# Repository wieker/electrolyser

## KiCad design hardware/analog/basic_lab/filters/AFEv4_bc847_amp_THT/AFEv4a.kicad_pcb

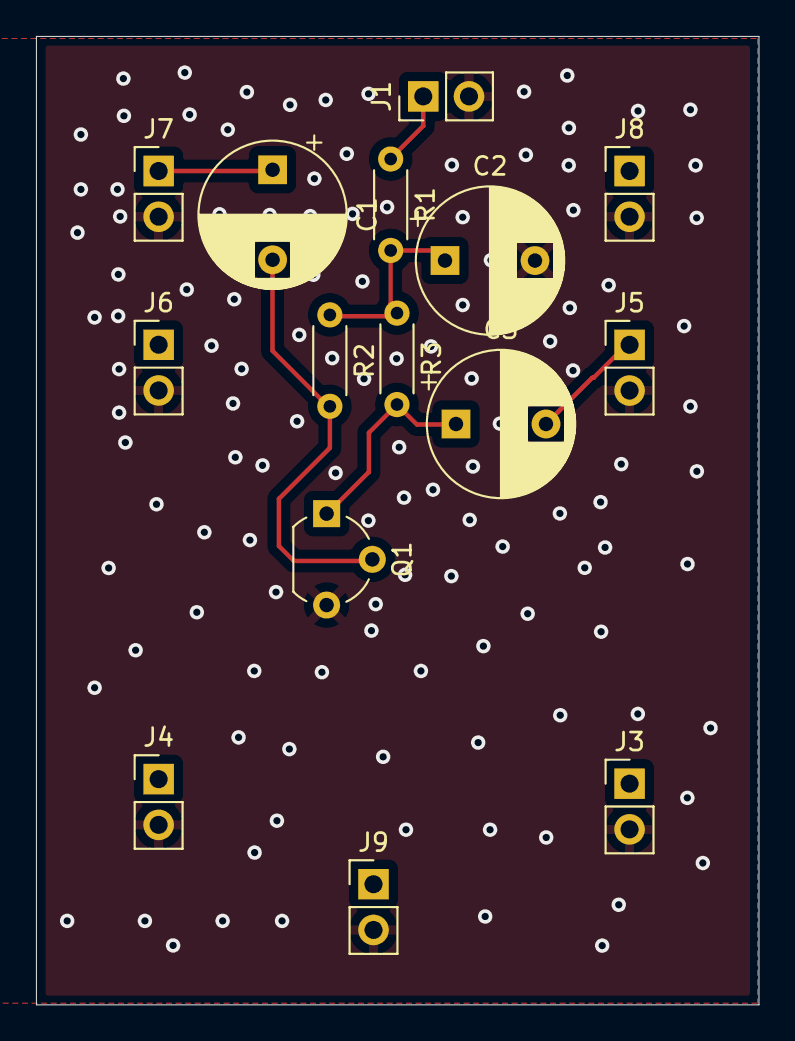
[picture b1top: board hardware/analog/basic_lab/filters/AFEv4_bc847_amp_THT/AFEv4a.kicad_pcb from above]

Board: 2 copper layers, 40.1 x 53.8 mm, 15 parts (0 on the bottom side), 7 nets.

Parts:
C1, C2, C3: C; CP_Radial_D8.0mm_P5.00mm
J1: Conn_01x02_Male; PinHeader_1x02_P2.54mm_Vertical
J3, J4, J5, J6, J7, J8, J9: Connector_Generic_Conn_01x02; PinHeader_1x02_P2.54mm_Vertical
Q1: BC547; TO-92_Wide
R1: R; R_Axial_DIN0204_L3.6mm_D1.6mm_P5.08mm_Horizontal
R2: 100 kOhm; R_Axial_DIN0204_L3.6mm_D1.6mm_P5.08mm_Horizontal
R3: 100 Ohm; R_Axial_DIN0204_L3.6mm_D1.6mm_P5.08mm_Horizontal

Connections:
GND: C2.2, J1.2, J3.2, J4.2, J5.2, J6.2, J7.2, J8.2, J9.2, Q1.3 (E)
unnamed: C1.2, Q1.2 (B), R2.2
unnamed: C2.1, R1.2, R2.1, R3.1
unnamed: C3.1, Q1.1 (C), R3.2
unnamed: J1.1, R1.1
bpf_ant: C3.2, J5.1
bpf_lvds: C1.1, J7.1

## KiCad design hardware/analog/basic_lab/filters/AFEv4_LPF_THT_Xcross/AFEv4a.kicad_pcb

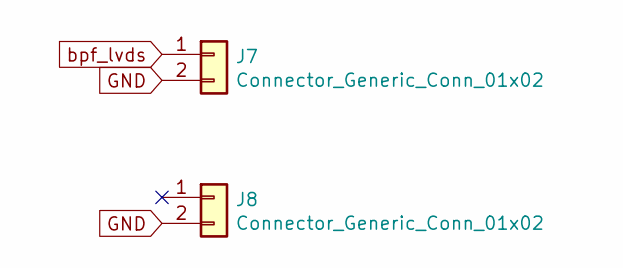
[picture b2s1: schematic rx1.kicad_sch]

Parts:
J7, J8: Connector_Generic_Conn_01x02; PinHeader_1x02_P2.54mm_Vertical

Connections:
GND: J7.2, J8.2; also elsewhere on the board
bpf_lvds: J7.1; also elsewhere on the board

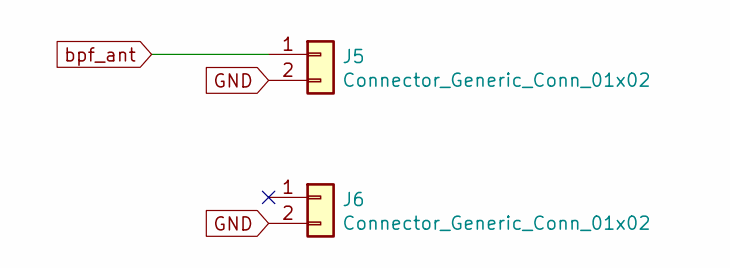
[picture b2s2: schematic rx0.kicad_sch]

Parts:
J5, J6: Connector_Generic_Conn_01x02; PinHeader_1x02_P2.54mm_Vertical

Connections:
GND: J5.2, J6.2; also elsewhere on the board
bpf_ant: J5.1; also elsewhere on the board

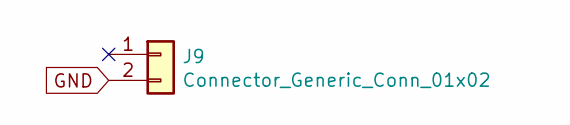
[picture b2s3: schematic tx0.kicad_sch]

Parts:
J9: Connector_Generic_Conn_01x02; PinHeader_1x02_P2.54mm_Vertical

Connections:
GND: J9.2; also elsewhere on the board

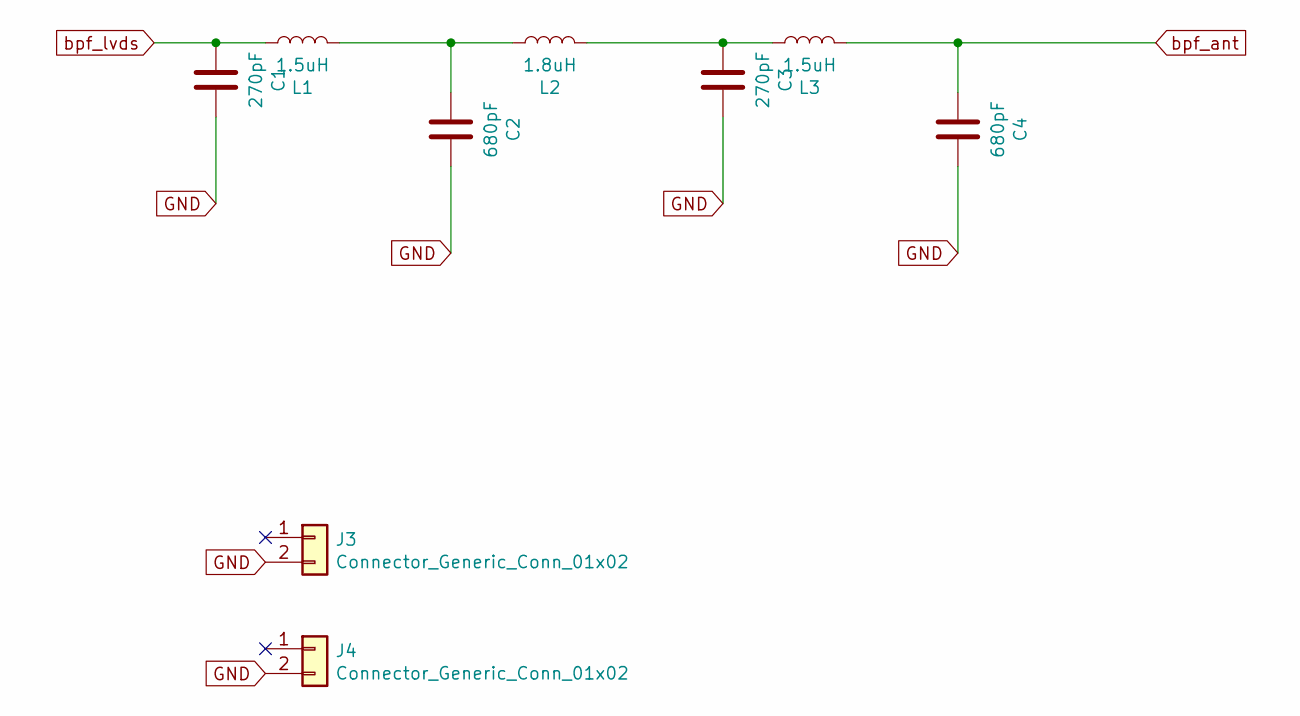
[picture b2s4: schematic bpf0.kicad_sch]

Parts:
C1, C3: 270pF; CP_Radial_D8.0mm_P5.00mm
C2, C4: 680pF; CP_Radial_D8.0mm_P5.00mm
J3, J4: Connector_Generic_Conn_01x02; PinHeader_1x02_P2.54mm_Vertical
L1, L3: 1.5uH; L_Axial_L9.5mm_D4.0mm_P12.70mm_Horizontal_Fastron_SMCC
L2: 1.8uH; L_Axial_L9.5mm_D4.0mm_P12.70mm_Horizontal_Fastron_SMCC

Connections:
GND: C1.1, C2.1, C3.1, C4.1, J3.2, J4.2; also elsewhere on the board
unnamed: C2.2, L1.2, L2.1
unnamed: C3.2, L2.2, L3.1
bpf_ant: C4.2, L3.2; also elsewhere on the board
bpf_lvds: C1.2, L1.1; also elsewhere on the board

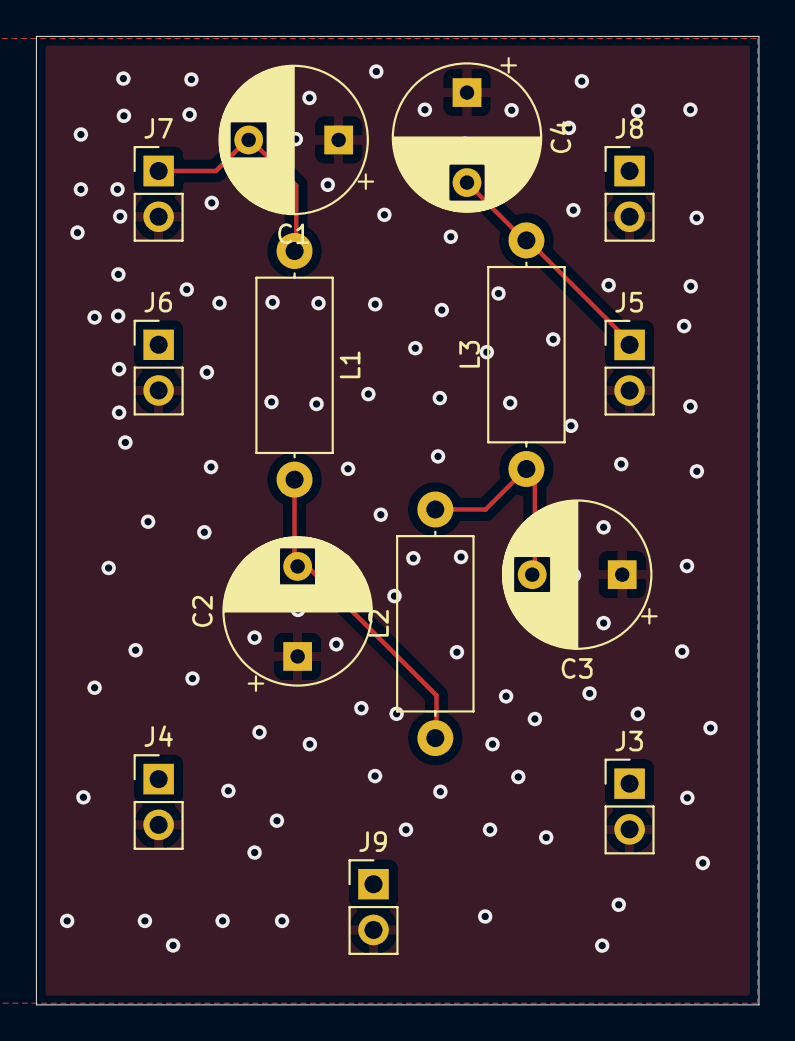
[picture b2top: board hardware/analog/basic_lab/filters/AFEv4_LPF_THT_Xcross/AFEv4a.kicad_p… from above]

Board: 2 copper layers, 40.1 x 53.8 mm, 14 parts (0 on the bottom side), 5 nets.

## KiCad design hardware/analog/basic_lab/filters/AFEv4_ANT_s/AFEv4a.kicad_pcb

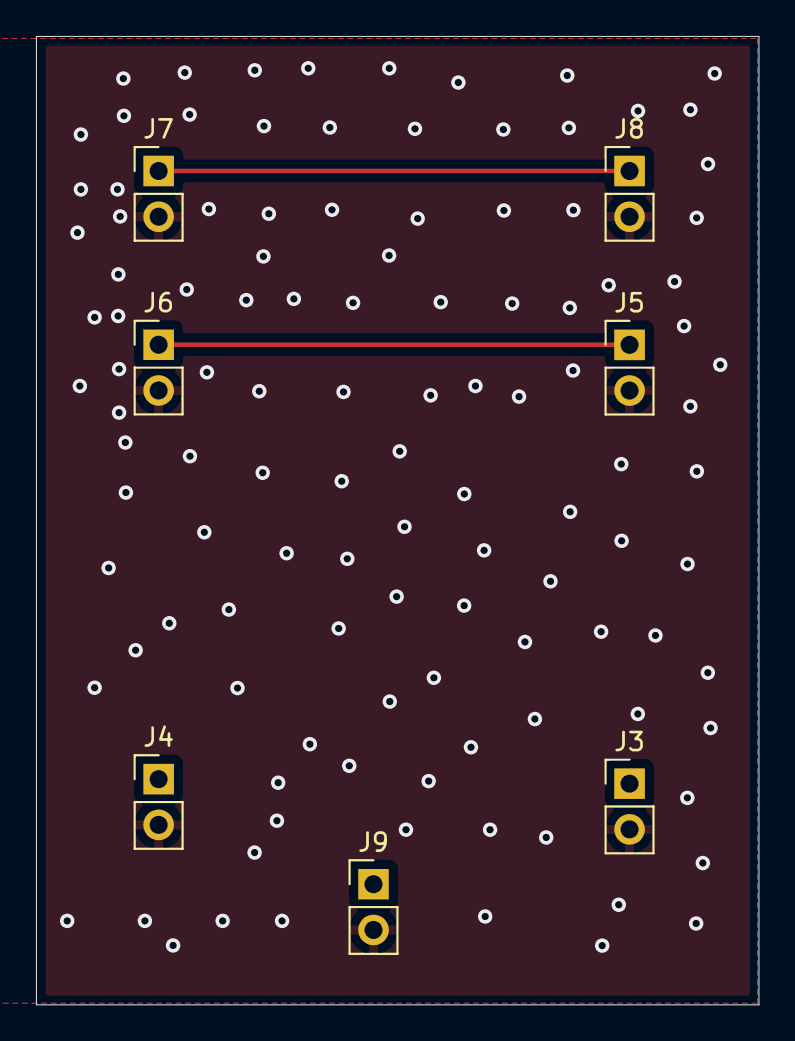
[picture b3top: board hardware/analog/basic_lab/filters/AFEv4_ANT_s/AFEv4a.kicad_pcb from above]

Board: 2 copper layers, 40.1 x 53.8 mm, 7 parts (0 on the bottom side), 3 nets.

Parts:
J3, J4, J5, J6, J7, J8, J9: Connector_Generic_Conn_01x02; PinHeader_1x02_P2.54mm_Vertical

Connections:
GND: J3.2, J4.2, J5.2, J6.2, J7.2, J8.2, J9.2
unnamed: J5.1, J6.1
bpf_lvds: J7.1, J8.1

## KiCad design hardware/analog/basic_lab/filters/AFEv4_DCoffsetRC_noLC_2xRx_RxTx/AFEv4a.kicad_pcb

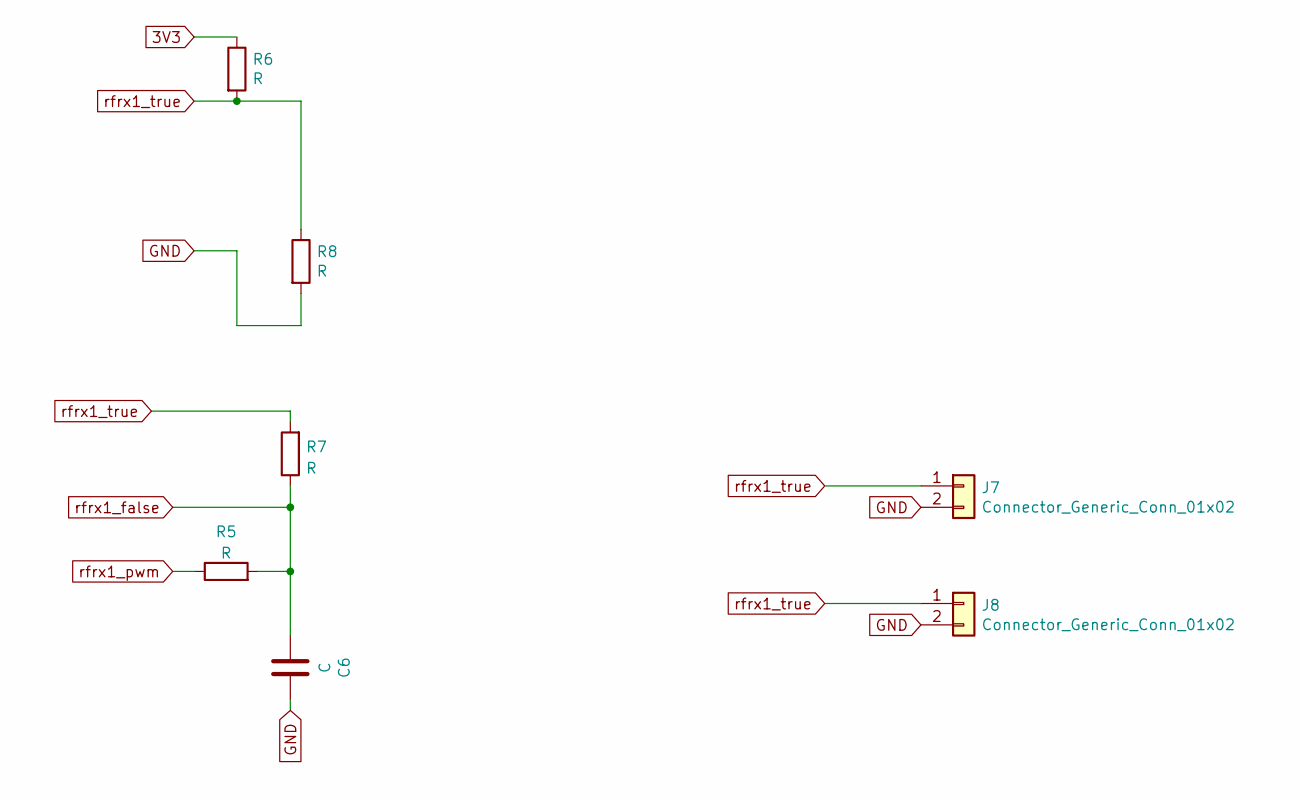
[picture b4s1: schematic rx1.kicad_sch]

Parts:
C6: C; C_Axial_L3.8mm_D2.6mm_P7.50mm_Horizontal
J7, J8: Connector_Generic_Conn_01x02; PinHeader_1x02_P2.54mm_Vertical
R5, R6, R7, R8: R; R_Axial_DIN0207_L6.3mm_D2.5mm_P5.08mm_Vertical

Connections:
3V3: R6.1; also elsewhere on the board
GND: C6.1, J7.2, J8.2, R8.2; also elsewhere on the board
rfrx1_false: C6.2, R5.2, R7.1; also elsewhere on the board
rfrx1_pwm: R5.1; also elsewhere on the board
rfrx1_true: J7.1, J8.1, R6.2, R7.2, R8.1; also elsewhere on the board

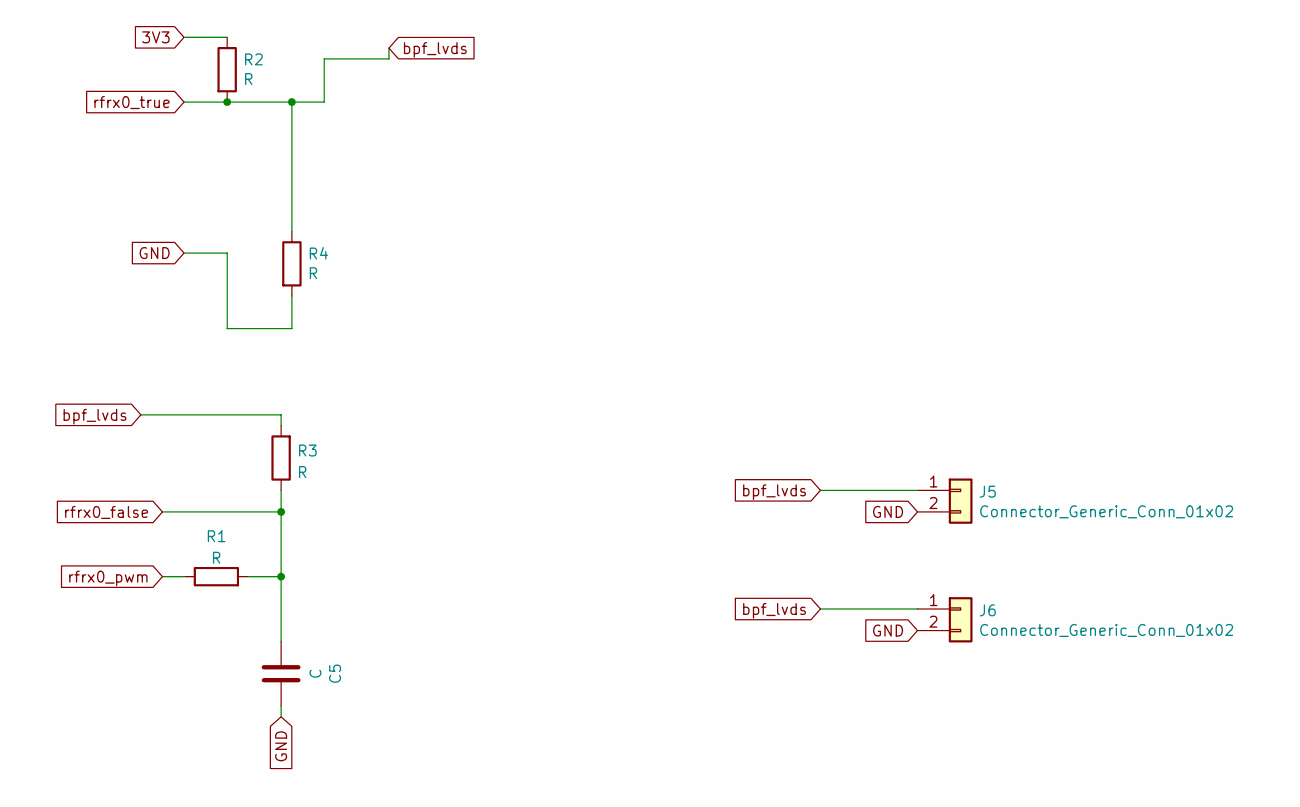
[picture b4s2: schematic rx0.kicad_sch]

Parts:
C5: C; C_1206_3216Metric
J5, J6: Connector_Generic_Conn_01x02; PinHeader_1x02_P2.54mm_Vertical
R1, R2, R3, R4: R; R_1206_3216Metric

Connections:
3V3: R2.1; also elsewhere on the board
GND: C5.1, J5.2, J6.2, R4.2; also elsewhere on the board
bpf_lvds: J5.1, J6.1, R2.2, R3.2, R4.1; also elsewhere on the board
rfrx0_false: C5.2, R1.2, R3.1; also elsewhere on the board
rfrx0_pwm: R1.1; also elsewhere on the board

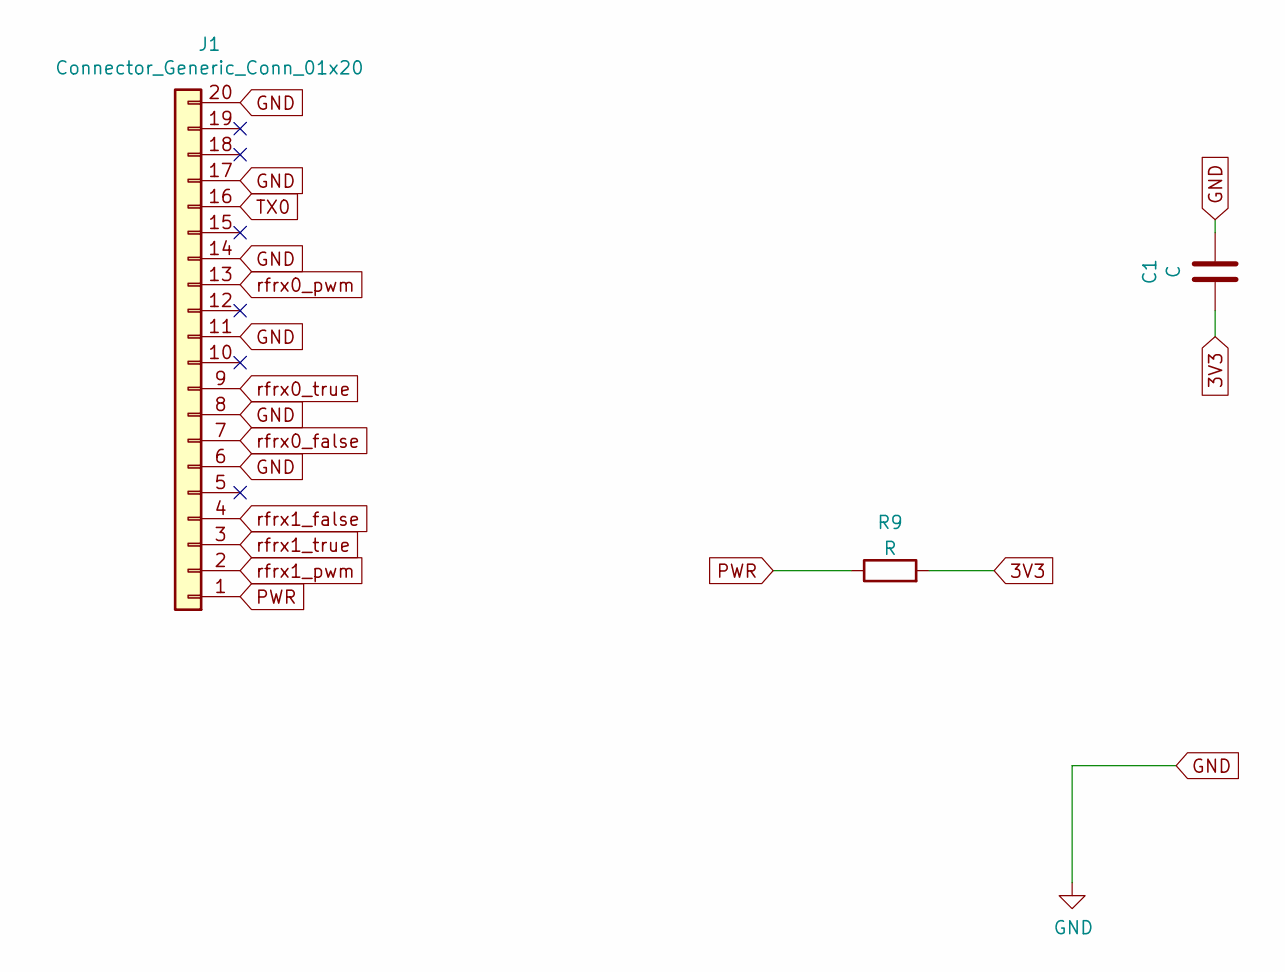
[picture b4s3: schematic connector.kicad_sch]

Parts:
C1: C; C_1206_3216Metric
J1: Connector_Generic_Conn_01x20; PinHeader_1x20_P2.54mm_Vertical
R9: R; R_0805_2012Metric

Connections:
3V3: C1.2, R9.2; also elsewhere on the board
GND: C1.1, J1.6, J1.8, J1.11, J1.14, J1.17, J1.20; also elsewhere on the board
PWR: J1.1, R9.1
TX0: J1.16; also elsewhere on the board
bpf_lvds: J1.9; also elsewhere on the board
rfrx0_false: J1.7; also elsewhere on the board
rfrx0_pwm: J1.13; also elsewhere on the board
rfrx1_false: J1.4; also elsewhere on the board
rfrx1_pwm: J1.2; also elsewhere on the board
rfrx1_true: J1.3; also elsewhere on the board

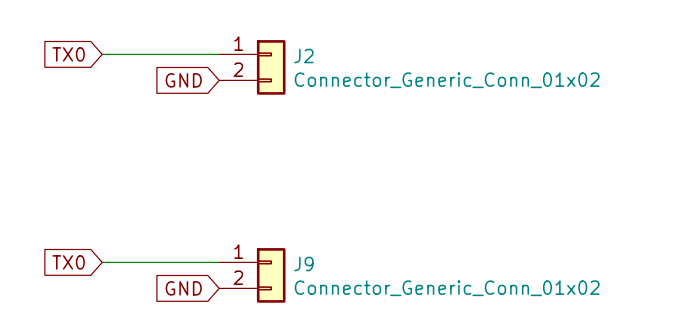
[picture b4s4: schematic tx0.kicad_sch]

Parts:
J2, J9: Connector_Generic_Conn_01x02; PinHeader_1x02_P2.54mm_Vertical

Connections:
GND: J2.2, J9.2; also elsewhere on the board
TX0: J2.1, J9.1; also elsewhere on the board

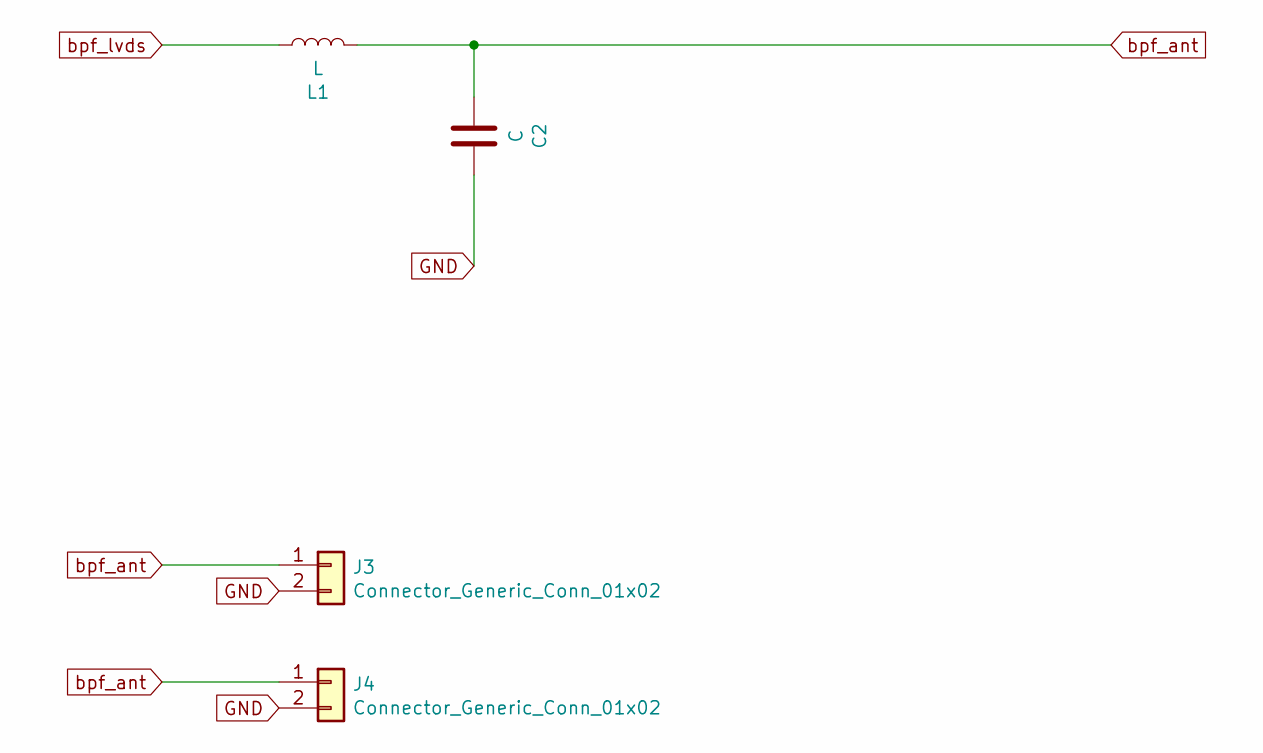
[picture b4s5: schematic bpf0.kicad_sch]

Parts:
C2: C; C_1206_3216Metric
J3, J4: Connector_Generic_Conn_01x02; PinHeader_1x02_P2.54mm_Vertical
L1: L; L_1206_3216Metric

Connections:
GND: C2.1, J3.2, J4.2; also elsewhere on the board
bpf_ant: C2.2, J3.1, J4.1, L1.2
bpf_lvds: L1.1; also elsewhere on the board

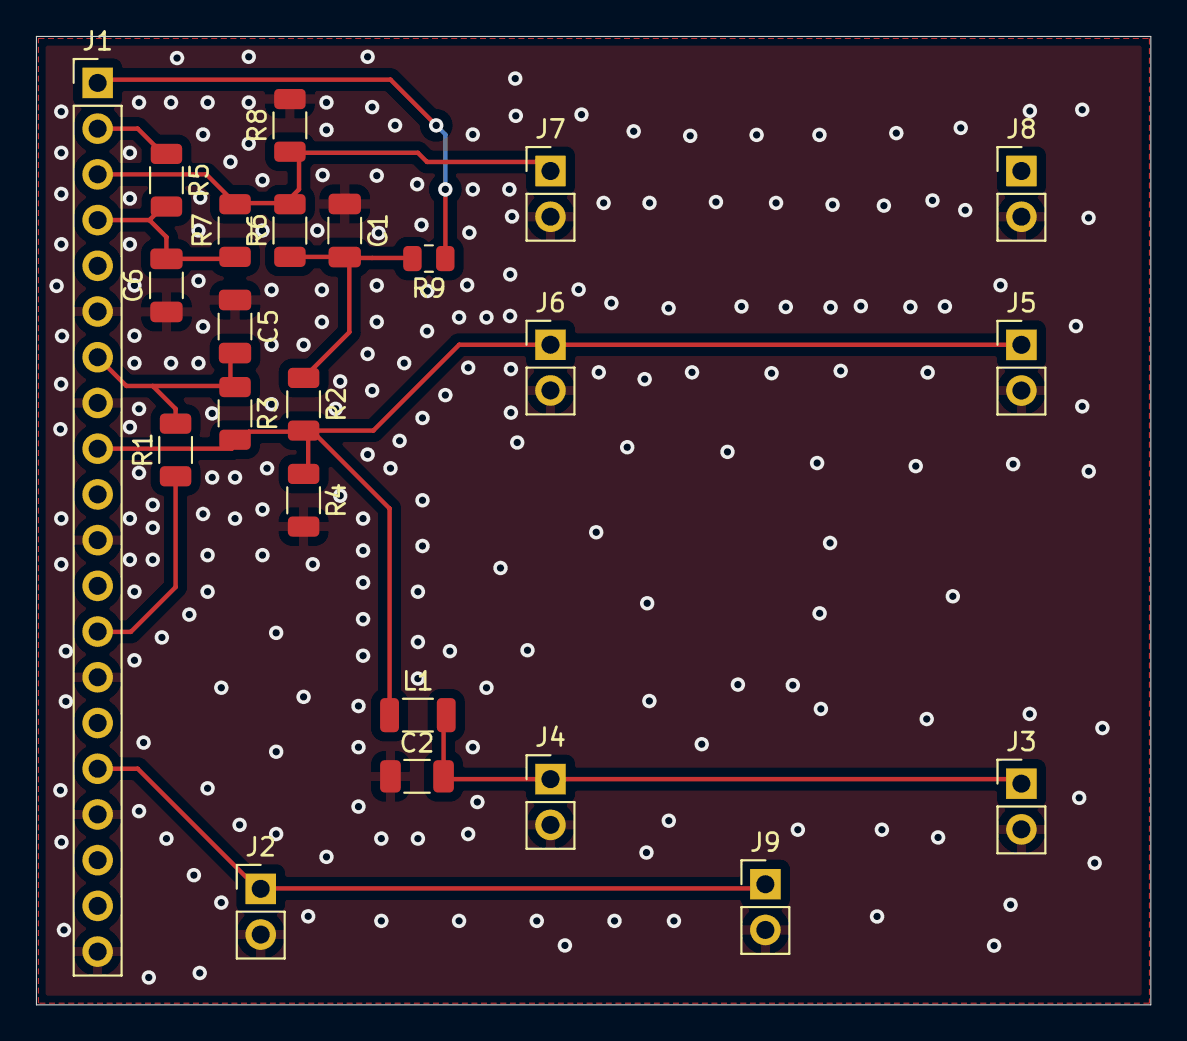
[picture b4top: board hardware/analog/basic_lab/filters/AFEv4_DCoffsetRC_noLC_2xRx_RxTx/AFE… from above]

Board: 2 copper layers, 61.9 x 53.8 mm, 23 parts (0 on the bottom side), 11 nets.

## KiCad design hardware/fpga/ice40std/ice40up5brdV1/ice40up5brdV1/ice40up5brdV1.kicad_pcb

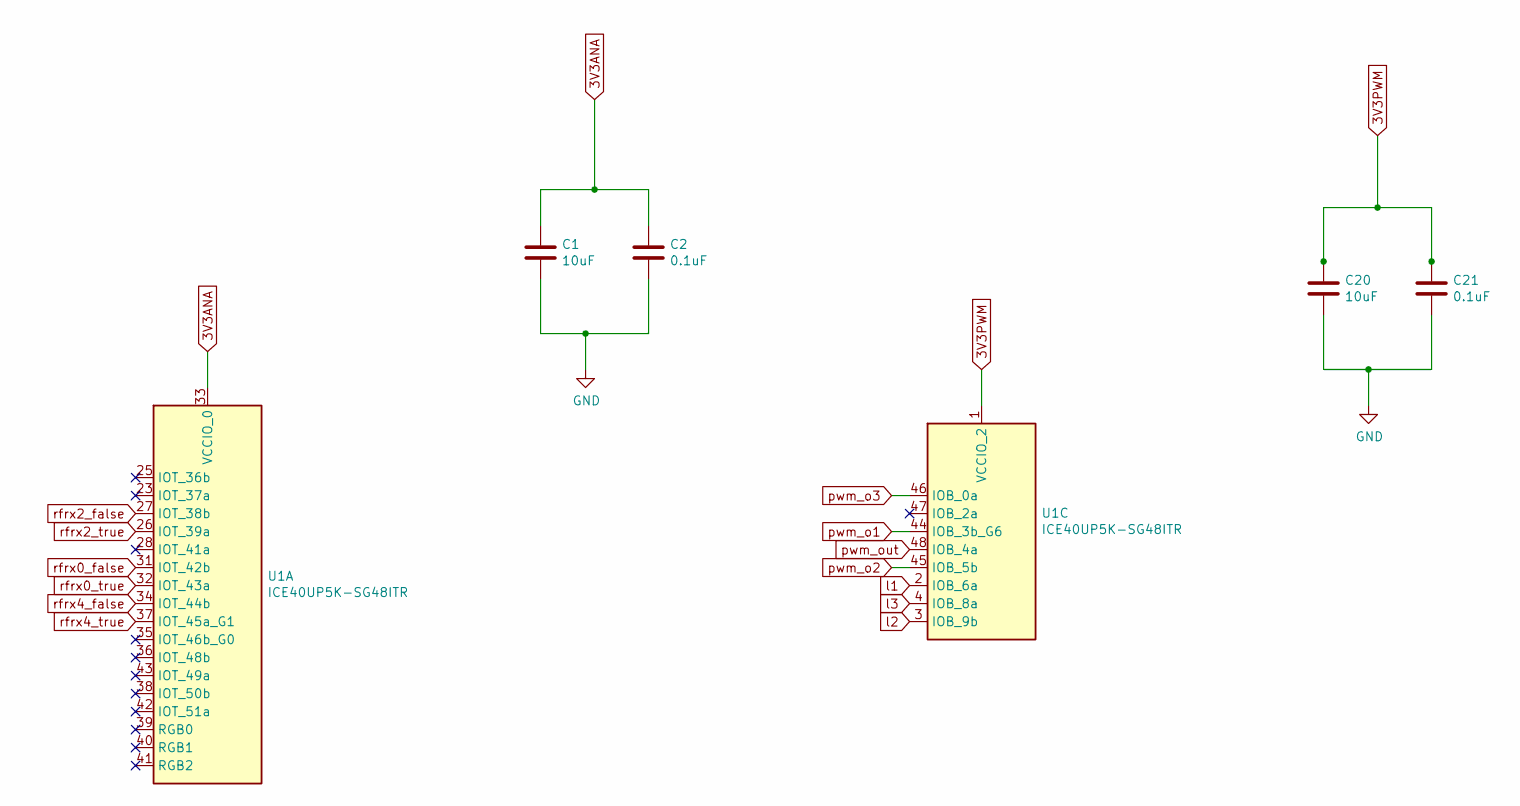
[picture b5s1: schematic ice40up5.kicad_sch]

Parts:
C1, C20: 10uF; C_0603_1608Metric
C2, C21: 0.1uF; C_0402_1005Metric
U1: ICE40UP5K-SG48ITR; QFN-48-1EP_7x7mm_P0.5mm_EP5.6x5.6mm

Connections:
3V3ANA: C1.1, C2.1, U1.33 (VCCIO_0); also elsewhere on the board
3V3PWM: C20.1, C21.1, U1.1 (VCCIO_2); also elsewhere on the board
GND: C1.2, C2.2, C20.2, C21.2; also elsewhere on the board
l1: U1.2 (IOB_6a); also elsewhere on the board
l2: U1.3 (IOB_9b); also elsewhere on the board
l3: U1.4 (IOB_8a); also elsewhere on the board
pwm_o1: U1.44 (IOB_3b_G6); also elsewhere on the board
pwm_o2: U1.45 (IOB_5b); also elsewhere on the board
pwm_o3: U1.46 (IOB_0a); also elsewhere on the board
pwm_out: U1.48 (IOB_4a); also elsewhere on the board
rfrx0_false: U1.31 (IOT_42b); also elsewhere on the board
rfrx0_true: U1.32 (IOT_43a); also elsewhere on the board
rfrx2_false: U1.27 (IOT_38b); also elsewhere on the board
rfrx2_true: U1.26 (IOT_39a); also elsewhere on the board
rfrx4_false: U1.34 (IOT_44b); also elsewhere on the board
rfrx4_true: U1.37 (IOT_45a_G1); also elsewhere on the board

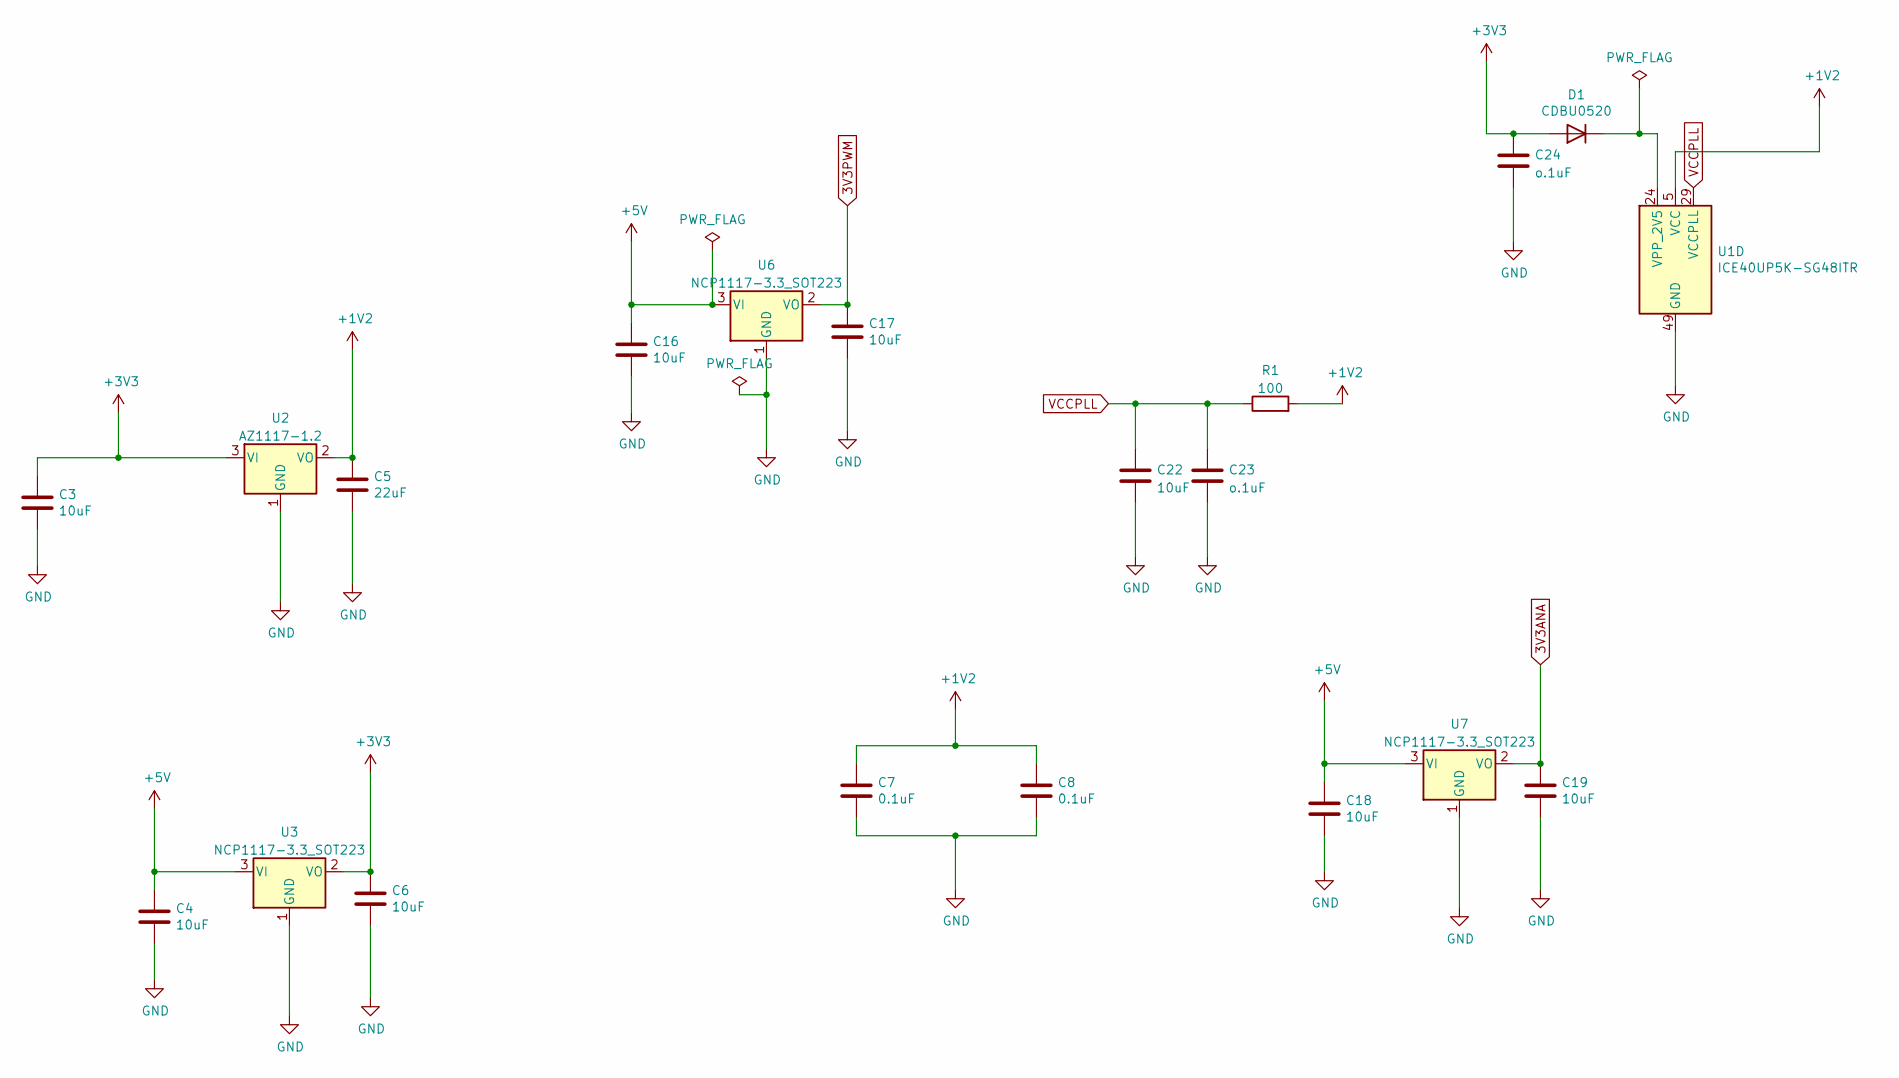
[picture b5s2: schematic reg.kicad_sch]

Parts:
C3, C4, C6, C16, C17, C18, C19, C22: 10uF; C_0603_1608Metric
C5: 22uF; C_1206_3216Metric
C7, C8: 0.1uF; C_0402_1005Metric
C23, C24: o.1uF; C_0402_1005Metric
D1: CDBU0520; D_0603_1608Metric
R1: 100; R_0805_2012Metric
U1: ICE40UP5K-SG48ITR; QFN-48-1EP_7x7mm_P0.5mm_EP5.6x5.6mm
U2: AZ1117-1.2; SOT-223-3_TabPin2
U3, U6, U7: NCP1117-3.3_SOT223; SOT-223-3_TabPin2

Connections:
3V3ANA: C19.1, U7.2 (VO); also elsewhere on the board
3V3PWM: C17.1, U6.2 (VO); also elsewhere on the board
+1V2: C5.1, C7.1, C8.1, R1.2, U1.5 (VCC), U1.30 (VCC), U2.2 (VO)
+3V3: C3.1, C6.1, C24.1, D1.2 (A), U2.3 (VI), U3.2 (VO); also elsewhere on the board
+5V: C4.1, C16.1, C18.1, U3.3 (VI), U6.3 (VI), U7.3 (VI); also elsewhere on the board
GND: C3.2, C4.2, C5.2, C6.2, C7.2, C8.2, C16.2, C17.2, C18.2, C19.2, C22.2, C23.2, C24.2, U1.49 (GND), U2.1 (GND), U3.1 (GND), U6.1 (GND), U7.1 (GND); also elsewhere on the board
unnamed: D1.1 (K), U1.24 (VPP_2V5)
VCCPLL: C22.1, C23.1, R1.1, U1.29 (VCCPLL)

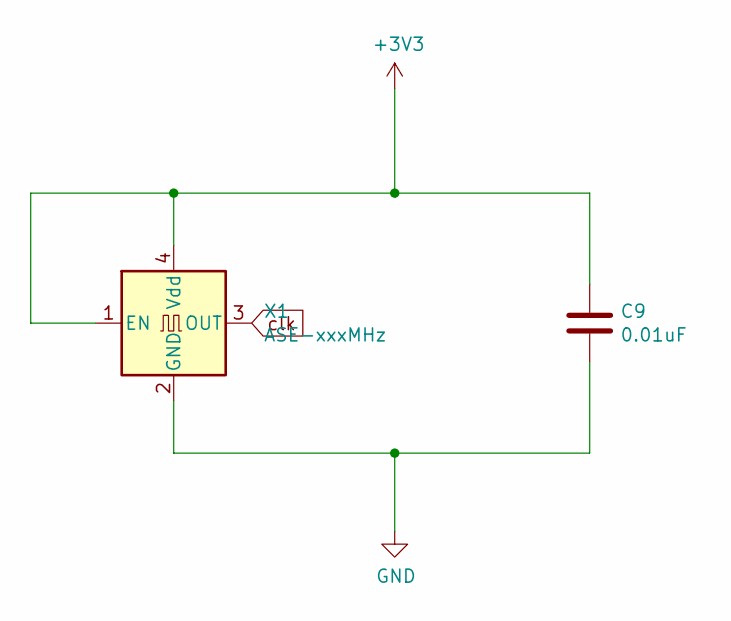
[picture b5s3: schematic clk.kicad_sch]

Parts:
C9: 0.01uF; C_0402_1005Metric
X1: ASE-xxxMHz; Oscillator_SMD_Abracon_ASE-4Pin_3.2x2.5mm

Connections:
+3V3: C9.1, X1.1 (EN), X1.4 (Vdd); also elsewhere on the board
GND: C9.2, X1.2 (GND); also elsewhere on the board
clk: X1.3 (OUT); also elsewhere on the board

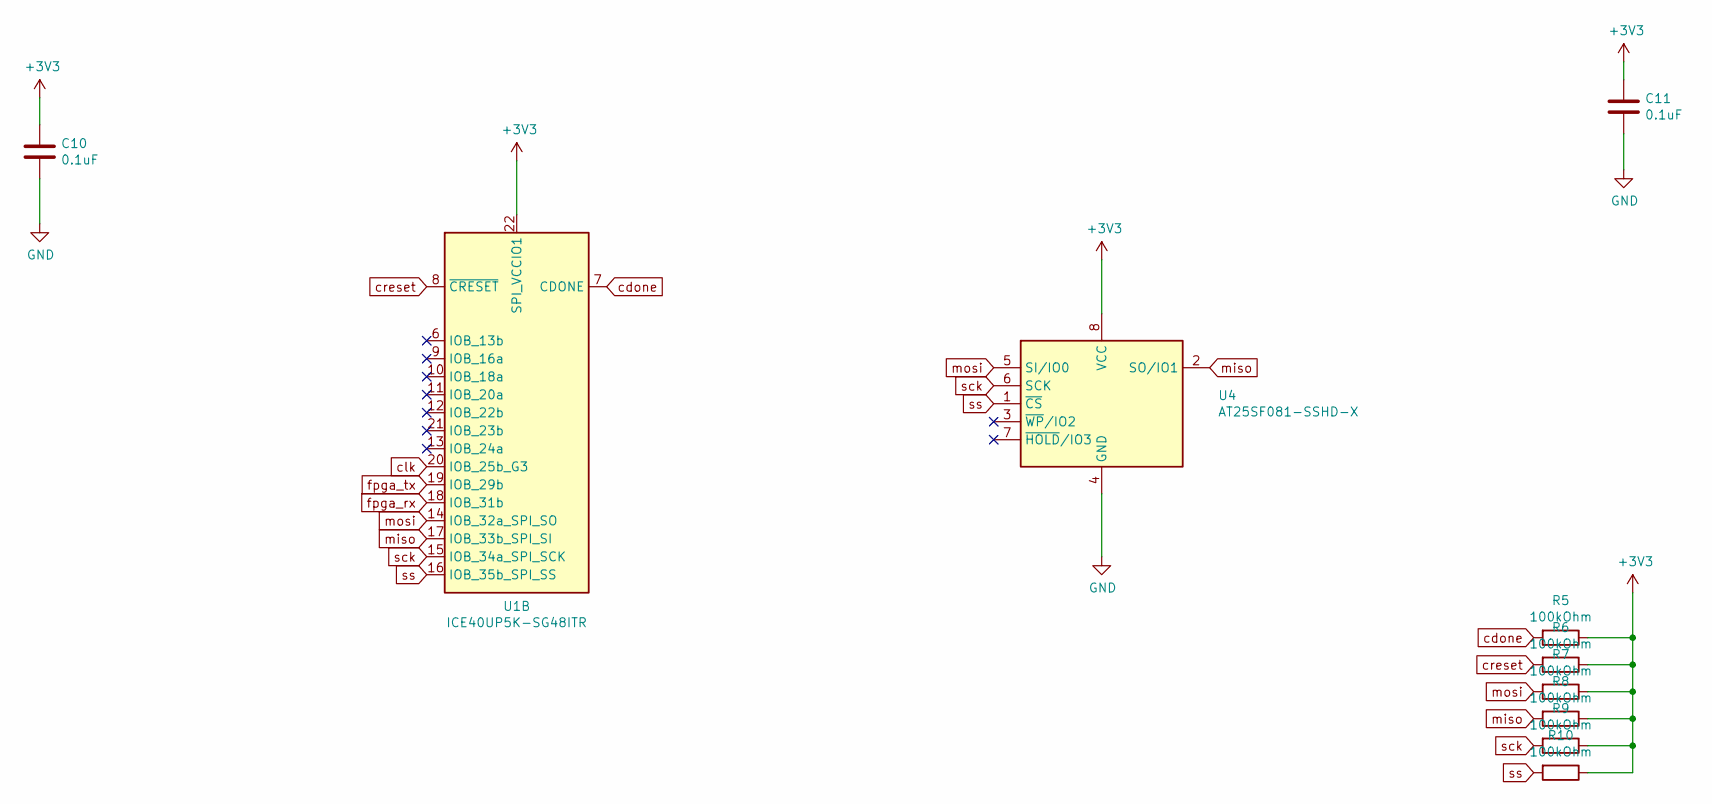
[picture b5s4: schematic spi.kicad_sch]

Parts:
C10, C11: 0.1uF; C_0402_1005Metric
R5, R6, R7, R8, R9, R10: 100kOhm; R_0402_1005Metric
U1: ICE40UP5K-SG48ITR; QFN-48-1EP_7x7mm_P0.5mm_EP5.6x5.6mm
U4: AT25SF081-SSHD-X; SOIC-8_3.9x4.9mm_P1.27mm

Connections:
+3V3: C10.1, C11.1, R5.1, R6.1, R7.1, R8.1, R9.1, R10.1, U1.22 (SPI_VCCIO1), U4.8 (VCC); also elsewhere on the board
GND: C10.2, C11.2, U4.4 (GND); also elsewhere on the board
cdone: R5.2, U1.7 (CDONE); also elsewhere on the board
clk: U1.20 (IOB_25b_G3); also elsewhere on the board
creset: R6.2, U1.8 (~CRESET); also elsewhere on the board
fpga_rx: U1.18 (IOB_31b); also elsewhere on the board
fpga_tx: U1.19 (IOB_29b); also elsewhere on the board
miso: R8.2, U1.17 (IOB_33b_SPI_SI), U4.2 (SO/IO1); also elsewhere on the board
mosi: R7.2, U1.14 (IOB_32a_SPI_SO), U4.5 (SI/IO0); also elsewhere on the board
sck: R9.2, U1.15 (IOB_34a_SPI_SCK), U4.6 (SCK); also elsewhere on the board
ss: R10.2, U1.16 (IOB_35b_SPI_SS), U4.1 (~CS); also elsewhere on the board

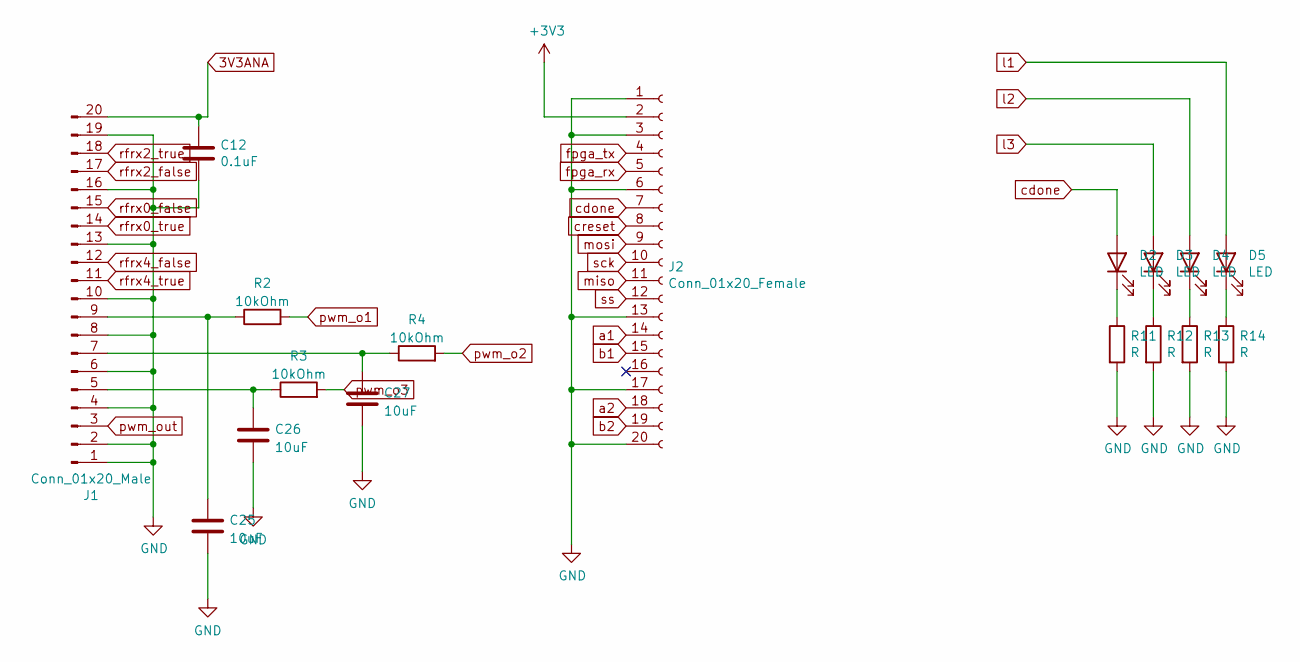
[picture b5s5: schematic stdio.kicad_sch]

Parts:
C12: 0.1uF; C_0402_1005Metric
C25, C26, C27: 10uF; C_0603_1608Metric
D2, D3, D4, D5: LED; LED_1206_3216Metric
J1: Conn_01x20_Male; PinHeader_1x20_P2.54mm_Horizontal
J2: Conn_01x20_Female; PinHeader_1x20_P2.54mm_Horizontal
R2, R3, R4: 10kOhm; R_0402_1005Metric
R11, R12, R13, R14: R; R_0402_1005Metric

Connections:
3V3ANA: C12.1, J1.20; also elsewhere on the board
+3V3: J2.2; also elsewhere on the board
GND: C12.2, C25.2, C26.2, C27.2, J1.1, J1.2, J1.4, J1.6, J1.8, J1.10, J1.13, J1.16, J1.19, J2.1, J2.3, J2.6, J2.13, J2.17, J2.20, R11.2, R12.2, R13.2, R14.2; also elsewhere on the board
unnamed: C25.1, J1.9, R2.1
unnamed: C26.1, J1.5, R3.1
unnamed: C27.1, J1.7, R4.1
unnamed: D2.1 (K), R11.1
unnamed: D3.1 (K), R12.1
unnamed: D4.1 (K), R13.1
unnamed: D5.1 (K), R14.1
a1: J2.14; also elsewhere on the board
a2: J2.18; also elsewhere on the board
b1: J2.15; also elsewhere on the board
b2: J2.19; also elsewhere on the board
cdone: D2.2 (A), J2.7; also elsewhere on the board
creset: J2.8; also elsewhere on the board
fpga_rx: J2.5; also elsewhere on the board
fpga_tx: J2.4; also elsewhere on the board
l1: D5.2 (A); also elsewhere on the board
l2: D4.2 (A); also elsewhere on the board
l3: D3.2 (A); also elsewhere on the board
miso: J2.11; also elsewhere on the board
mosi: J2.9; also elsewhere on the board
pwm_o1: R2.2; also elsewhere on the board
pwm_o2: R4.2; also elsewhere on the board
pwm_o3: R3.2; also elsewhere on the board
pwm_out: J1.3; also elsewhere on the board
rfrx0_false: J1.15; also elsewhere on the board
rfrx0_true: J1.14; also elsewhere on the board
rfrx2_false: J1.17; also elsewhere on the board
rfrx2_true: J1.18; also elsewhere on the board
rfrx4_false: J1.12; also elsewhere on the board
rfrx4_true: J1.11; also elsewhere on the board
sck: J2.10; also elsewhere on the board
ss: J2.12; also elsewhere on the board
